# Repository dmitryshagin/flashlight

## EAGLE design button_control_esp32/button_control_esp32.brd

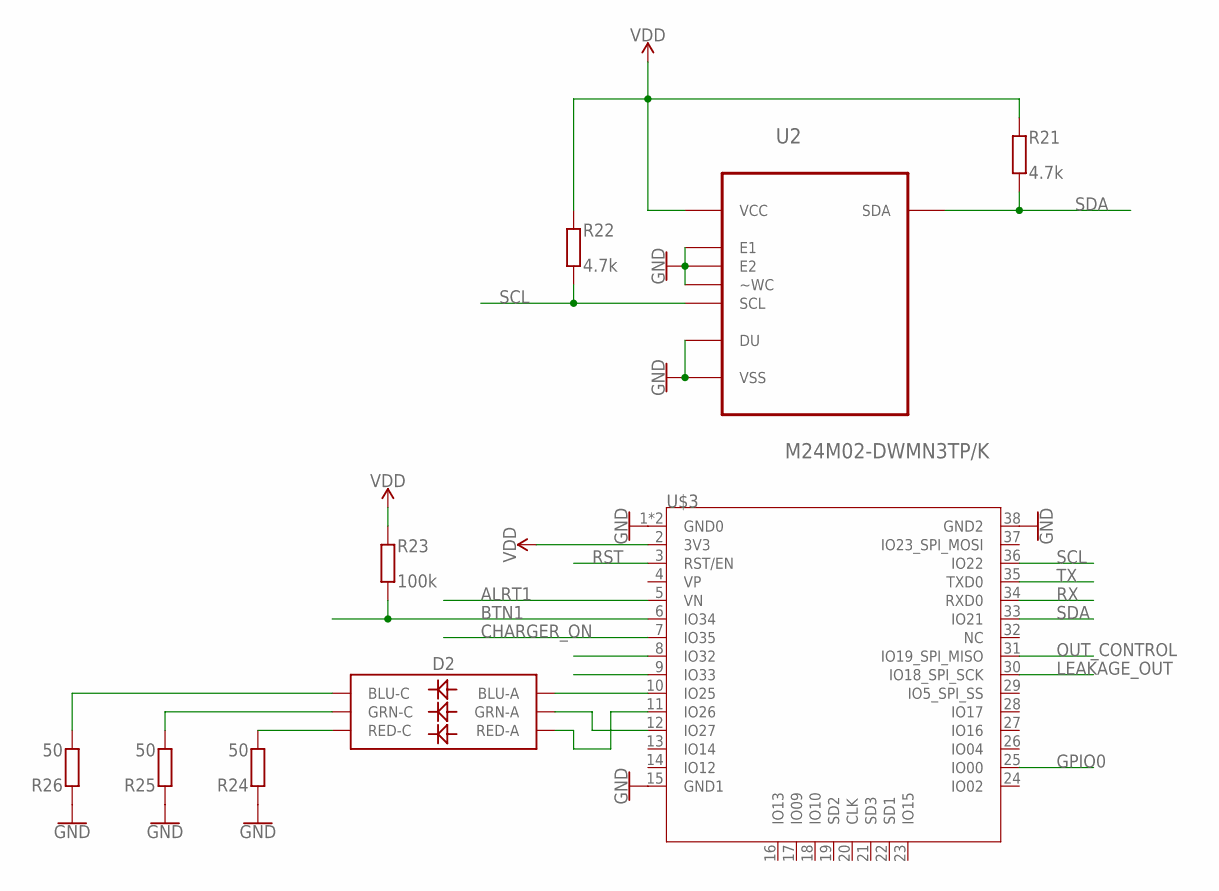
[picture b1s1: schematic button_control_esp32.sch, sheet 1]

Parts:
D2: LED-RGBNO_IC; LED-TRICOLOR-5050
R21, R22: 4.7k; R0603
R23: 100k; R0603
R24, R25, R26: 50; R0603
U2: M24M02-DWMN3TP/K; SOIC127P600X175-8N
U$3: ESP32; TTGO_ESP32

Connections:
ALRT1: U$3.5 (VN); also elsewhere on the board
BTN1: R23.1, U$3.6 (IO34); also elsewhere on the board
CHARGER_ON: U$3.7 (IO35); also elsewhere on the board
GND: R24.2, R25.2, R26.2, U2.1 (DU), U2.2 (E1), U2.3 (E2), U2.4 (VSS), U2.7 (~WC), U$3.1 (GND0), U$3.15 (GND1), U$3.38 (GND2), U$3.P$1 (GND0); also elsewhere on the board
GPIO0: U$3.25 (IO00); also elsewhere on the board
LEAKAGE_OUT: U$3.30 (IO18_SPI_SCK); also elsewhere on the board
unnamed: D2.3 (BLU-A), U$3.10 (IO25)
unnamed: D2.1 (GRN-A), U$3.12 (IO27)
unnamed: D2.2 (RED-A), U$3.11 (IO26)
unnamed: D2.4 (BLU-C), R26.1
unnamed: D2.6 (GRN-C), R25.1
unnamed: D2.5 (RED-C), R24.1
OUT_CONTROL: U$3.31 (IO19_SPI_MISO); also elsewhere on the board
RST: U$3.3 (RST/EN); also elsewhere on the board
RX: U$3.34 (RXD0); also elsewhere on the board
SCL: R22.1, U2.6 (SCL), U$3.36 (IO22); also elsewhere on the board
SDA: R21.1, U2.5 (SDA), U$3.33 (IO21); also elsewhere on the board
TX: U$3.35 (TXD0); also elsewhere on the board
VDD: R21.2, R22.2, R23.2, U2.8 (VCC), U$3.2 (3V3); also elsewhere on the board

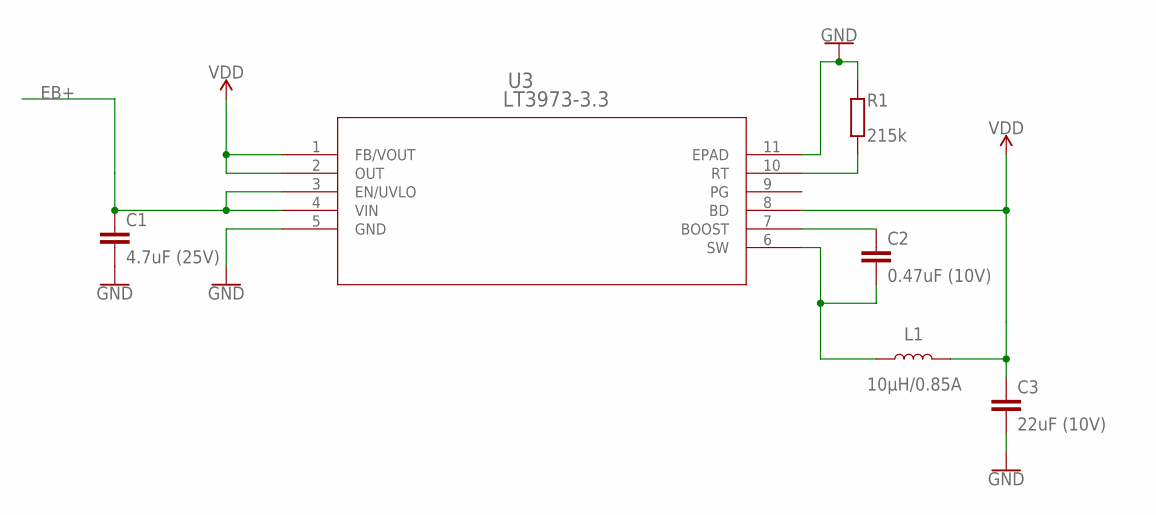
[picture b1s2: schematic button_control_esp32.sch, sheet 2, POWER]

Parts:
C1: 4.7uF (25V); C1206
C2: 0.47uF (10V); C0603K
C3: 22uF (10V); C1206
L1: 10µH/0.85A; INDUCTOR_4.7UH
R1: 215k; R0603
U3: LT3973-3.3; DFN-10_DD

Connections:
BOOST: C2.1, U3.7 (BOOST)
EB+: C1.1, U3.3 (EN/UVLO), U3.4 (VIN); also elsewhere on the board
GND: C1.2, C3.2, R1.2, U3.5 (GND), U3.11 (EPAD); also elsewhere on the board
RT: R1.1, U3.10 (RT)
SW: C2.2, L1.P$1 (1), U3.6 (SW)
VDD: C3.1, L1.P$2 (2), U3.1 (FB/VOUT), U3.2 (OUT), U3.8 (BD); also elsewhere on the board

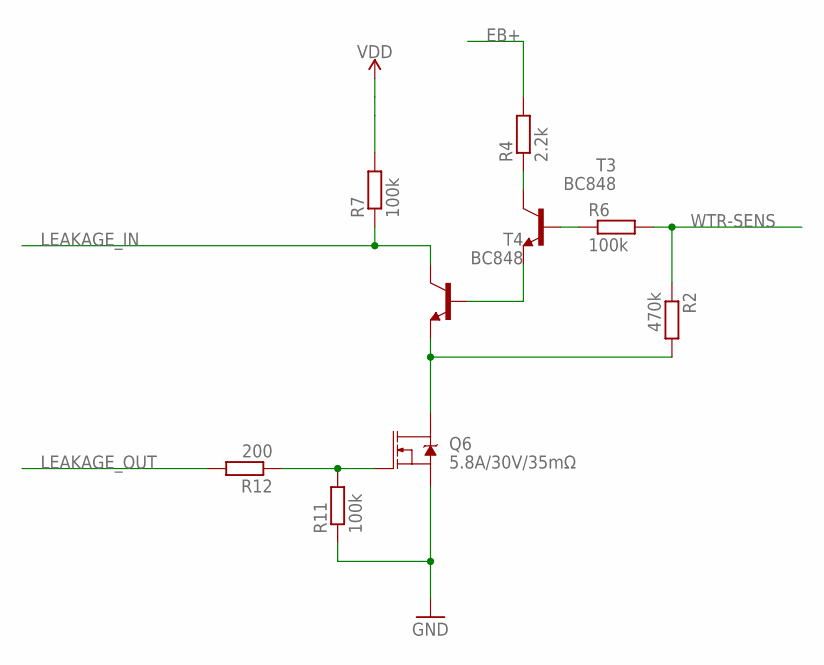
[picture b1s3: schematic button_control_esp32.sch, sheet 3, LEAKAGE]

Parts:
Q6: 5.8A/30V/35mΩ; SOT23-3
R2: 470k; R0603
R4: 2.2k; R0603
R6, R7, R11: 100k; R0603
R12: 200; R0603
T3, T4: BC848; SOT23

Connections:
EB+: R4.2; also elsewhere on the board
GND: Q6.2 (S), R11.1; also elsewhere on the board
LEAKAGE_IN: R7.1, T4.3 (C)
LEAKAGE_OUT: R12.2; also elsewhere on the board
unnamed: T3.2 (E), T4.1 (B)
unnamed: R6.1, T3.1 (B)
unnamed: Q6.3 (D), R2.2, T4.2 (E)
VDD: R7.2; also elsewhere on the board
WTR-SENS: R2.1, R6.2; also elsewhere on the board
WTR_MEASURE_ON1: Q6.1 (G), R11.2, R12.1
WTR_MEASURE_PULLUP1: R4.1, T3.3 (C)

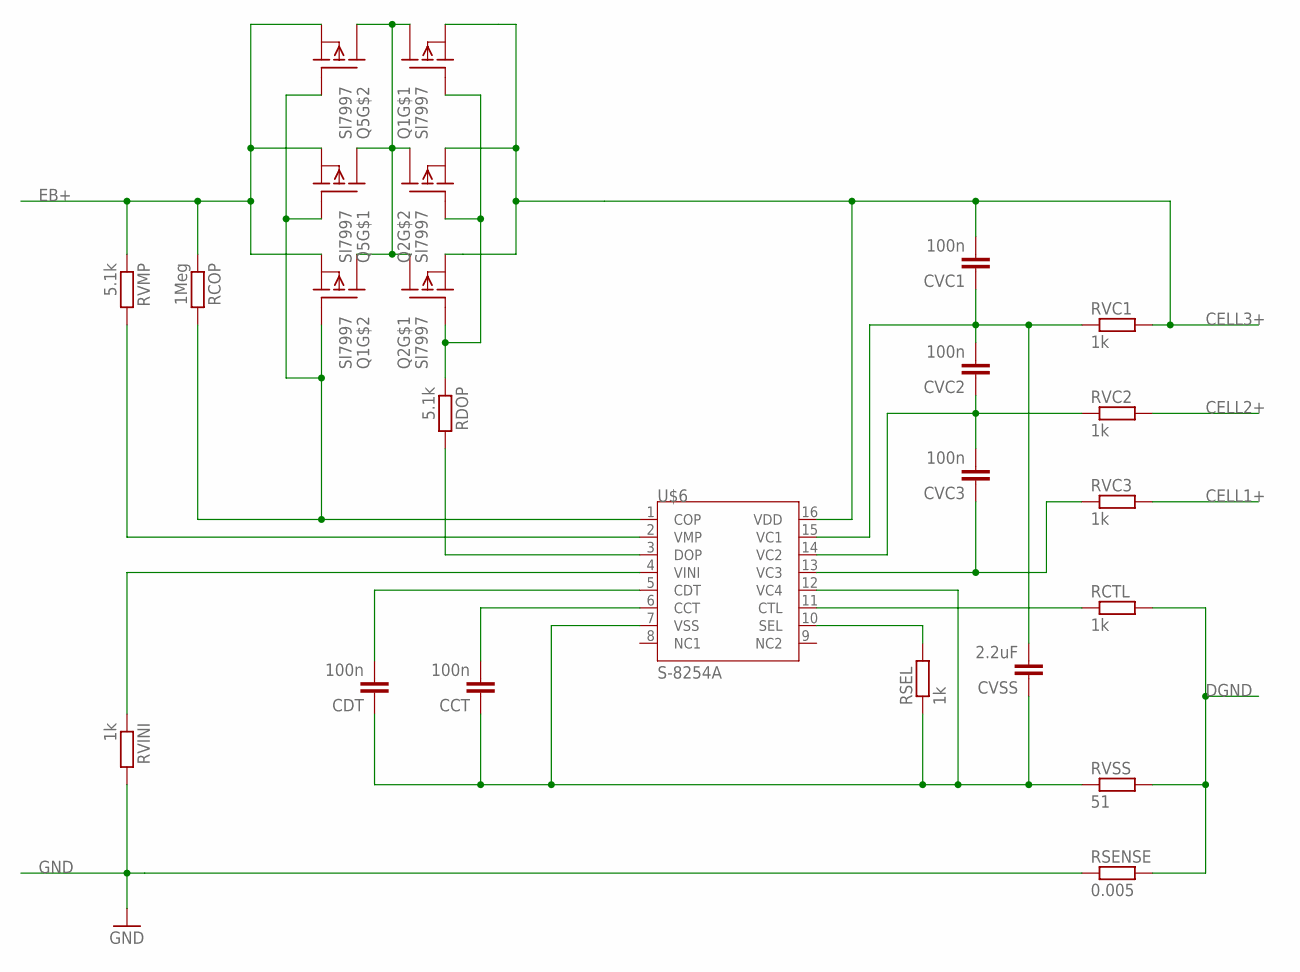
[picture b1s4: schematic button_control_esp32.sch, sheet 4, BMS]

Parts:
CCT: 100n; C0603
CDT: 100n; C0603
CVC1, CVC3: 100n; C0603
CVC2: 100n; C0805K
CVSS: 2.2uF; C0805
Q1, Q2, Q5: SI7997; POWERPAK
RCOP: 1Meg; R0603
RCTL: 1k; R0603
RDOP: 5.1k; R0603
RSEL: 1k; R0603
RSENSE: 0.005; R2010
RVC1, RVC2, RVC3: 1k; R0603
RVINI: 1k; R0603
RVMP: 5.1k; R0603
RVSS: 51; R0603
U$6: S-8254A; TSSOP-16

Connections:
CELL1+: RVC3.2; also elsewhere on the board
CELL2+: RVC2.2; also elsewhere on the board
CELL3+: CVC1.2, Q1.1 (S), Q2.1 (S), Q2.3 (S), RVC1.2, U$6.16 (VDD); also elsewhere on the board
DGND: RCTL.2, RSENSE.2, RVSS.2; also elsewhere on the board
EB+: Q1.3 (S), Q5.1 (S), Q5.3 (S), RCOP.1, RVMP.1; also elsewhere on the board
GND: RSENSE.1, RVINI.2; also elsewhere on the board
unnamed: RDOP.2, U$6.3 (DOP)
unnamed: Q1.4 (G), Q5.2 (G), Q5.4 (G), RCOP.2, U$6.1 (COP)
unnamed: Q1.2 (G), Q2.2 (G), Q2.4 (G), RDOP.1
unnamed: RVMP.2, U$6.2 (VMP)
unnamed: RSEL.2, U$6.10 (SEL)
unnamed: RVINI.1, U$6.4 (VINI)
unnamed: CDT.2, U$6.5 (CDT)
unnamed: CCT.2, U$6.6 (CCT)
unnamed: CCT.1, CDT.1, CVSS.1, RSEL.1, RVSS.1, U$6.7 (VSS), U$6.12 (VC4)
unnamed: RCTL.1, U$6.11 (CTL)
unnamed: Q1.5 (D), Q1.5_6 (D), Q1.6 (D), Q1.7 (D), Q1.7_8 (D), Q1.8 (D), Q2.5 (D), Q2.5_6 (D), Q2.6 (D), Q2.7 (D), Q2.7_8 (D), Q2.8 (D), Q5.5 (D), Q5.5_6 (D), Q5.6 (D), Q5.7 (D), Q5.7_8 (D), Q5.8 (D)
unnamed: CVC3.1, RVC3.1, U$6.13 (VC3)
unnamed: CVC2.1, CVC3.2, RVC2.1, U$6.14 (VC2)
unnamed: CVC1.1, CVC2.2, CVSS.2, RVC1.1, U$6.15 (VC1)

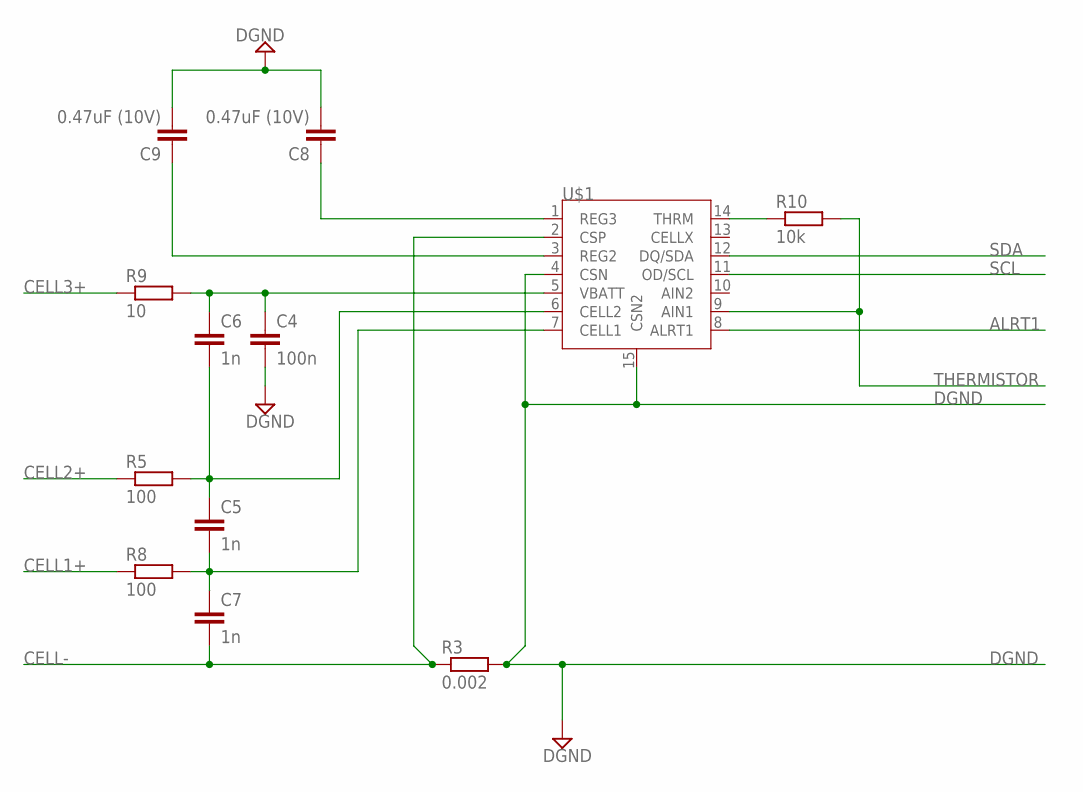
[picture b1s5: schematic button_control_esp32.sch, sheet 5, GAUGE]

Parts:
C4: 100n; C0603
C5, C6, C7: 1n; C0603
C8, C9: 0.47uF (10V); C0603K
R3: 0.002; R2010
R5, R8: 100; R0805
R9: 10; R0603
R10: 10k; R0603
U$1: MAX17205G; SON40P300X300X80-15N230X170

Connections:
ALRT1: U$1.8 (ALRT1); also elsewhere on the board
CELL1+: R8.1; also elsewhere on the board
CELL2+: R5.1; also elsewhere on the board
CELL3+: R9.1; also elsewhere on the board
CELL-: C7.2, R3.1, U$1.2 (CSP); also elsewhere on the board
DGND: C4.2, C8.2, C9.2, R3.2, U$1.4 (CSN), U$1.15 (CSN2); also elsewhere on the board
unnamed: C4.1, C6.1, R9.2, U$1.5 (VBATT)
unnamed: C5.1, C6.2, R5.2, U$1.6 (CELL2)
unnamed: C5.2, C7.1, R8.2, U$1.7 (CELL1)
unnamed: R10.1, U$1.14 (THRM)
unnamed: C8.1, U$1.1 (REG3)
unnamed: C9.1, U$1.3 (REG2)
SCL: U$1.11 (OD/SCL); also elsewhere on the board
SDA: U$1.12 (DQ/SDA); also elsewhere on the board
THERMISTOR: R10.2, U$1.9 (AIN1); also elsewhere on the board

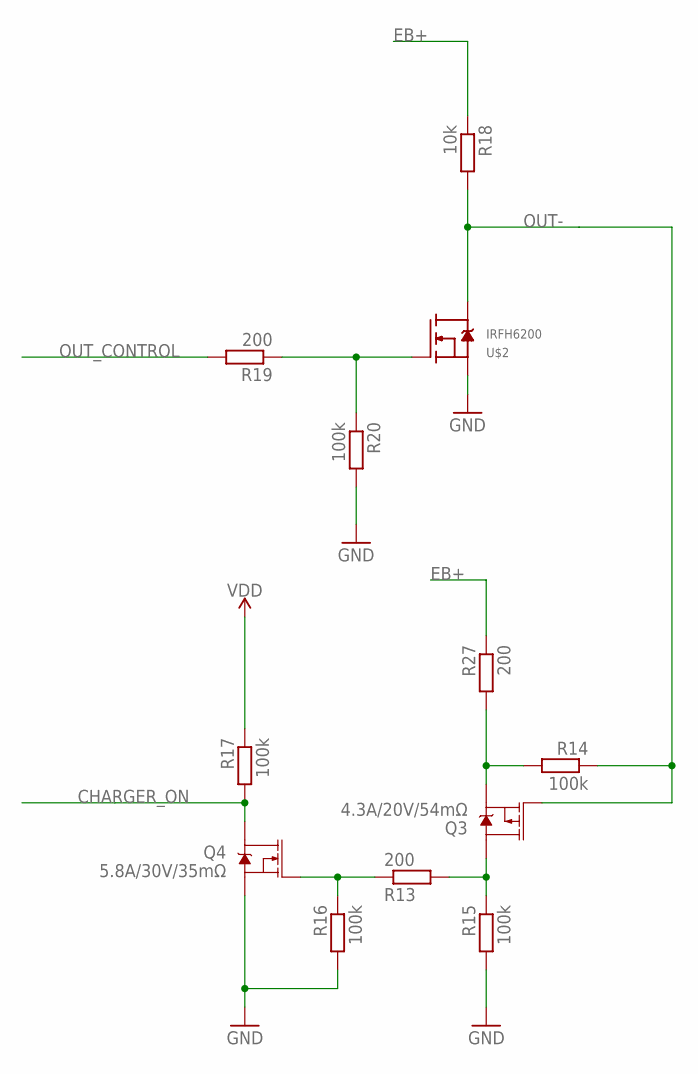
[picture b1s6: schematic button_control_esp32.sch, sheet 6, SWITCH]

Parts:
Q3: 4.3A/20V/54mΩ; SOT23-3
Q4: 5.8A/30V/35mΩ; SOT23-3
R13, R19, R27: 200; R0603
R14, R15, R16, R17, R20: 100k; R0603
R18: 10k; R0603
U$2: IRFH6200; PQFN

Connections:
CHARGER_ON: Q4.3 (D), R17.2; also elsewhere on the board
EB+: R18.1, R27.1; also elsewhere on the board
GND: Q4.2 (S), R15.2, R16.2, R20.2, U$2.1 (S), U$2.2 (S), U$2.3 (S); also elsewhere on the board
unnamed: Q3.3 (D), R13.2, R15.1
unnamed: Q4.1 (G), R13.1, R16.1
unnamed: Q3.2 (S), R14.2, R27.2
OUT-: Q3.1 (G), R14.1, R18.2, U$2.5 (D), U$2.6 (D), U$2.7 (D), U$2.8 (D), U$2.9 (D); also elsewhere on the board
OUT_BASE: R19.1, R20.1, U$2.4 (G)
OUT_CONTROL: R19.2; also elsewhere on the board
VDD: R17.1; also elsewhere on the board

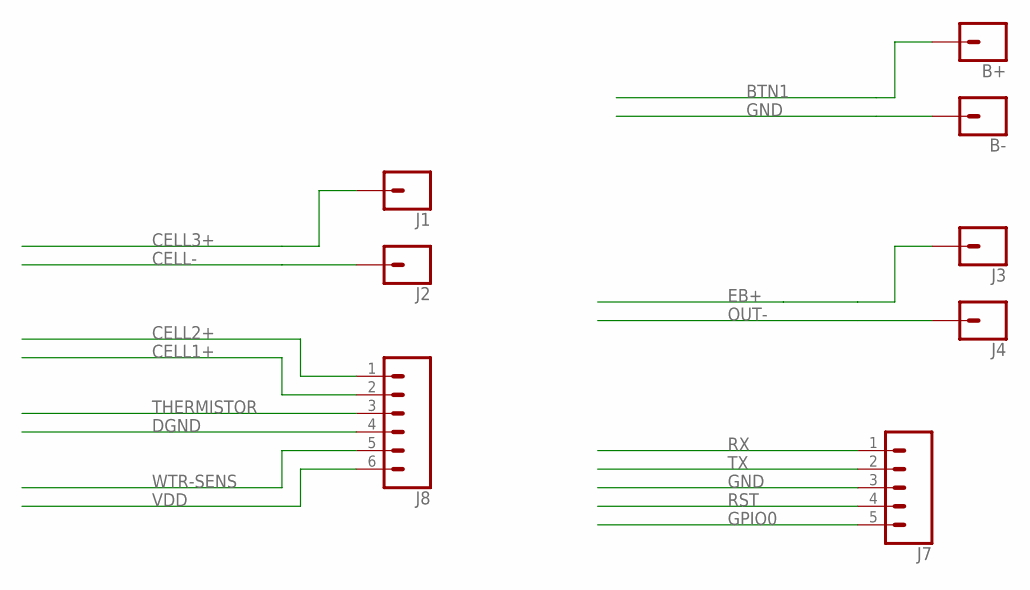
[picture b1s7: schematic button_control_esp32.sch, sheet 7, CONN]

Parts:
B+: CONN_01; 1X01
B-: CONN_01; 1X01
J1, J2, J3, J4: CONN_01PTH_2MM; 1X01_2MM
J7: CONN_051.27MM; 1X05_1.27MM
J8: CONN_061.27MM; 1X06_1.27MM

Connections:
BTN1: B+.1; also elsewhere on the board
CELL1+: J8.2; also elsewhere on the board
CELL2+: J8.1; also elsewhere on the board
CELL3+: J1.1; also elsewhere on the board
CELL-: J2.1; also elsewhere on the board
DGND: J8.4; also elsewhere on the board
EB+: J3.1; also elsewhere on the board
GND: B-.1, J7.3; also elsewhere on the board
GPIO0: J7.5; also elsewhere on the board
OUT-: J4.1; also elsewhere on the board
RST: J7.4; also elsewhere on the board
RX: J7.1; also elsewhere on the board
THERMISTOR: J8.3; also elsewhere on the board
TX: J7.2; also elsewhere on the board
VDD: J8.6; also elsewhere on the board
WTR-SENS: J8.5; also elsewhere on the board

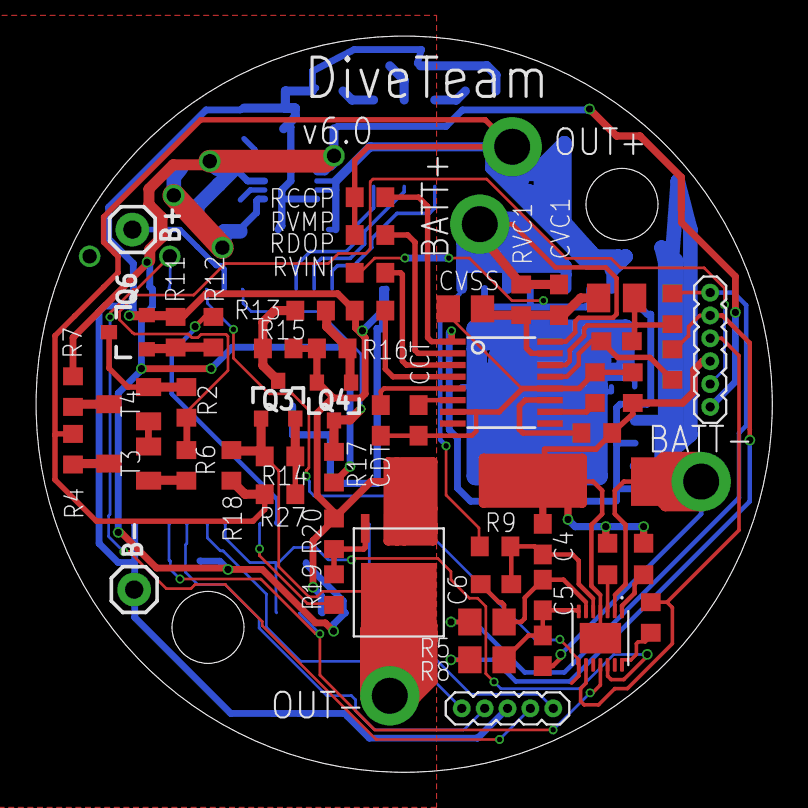
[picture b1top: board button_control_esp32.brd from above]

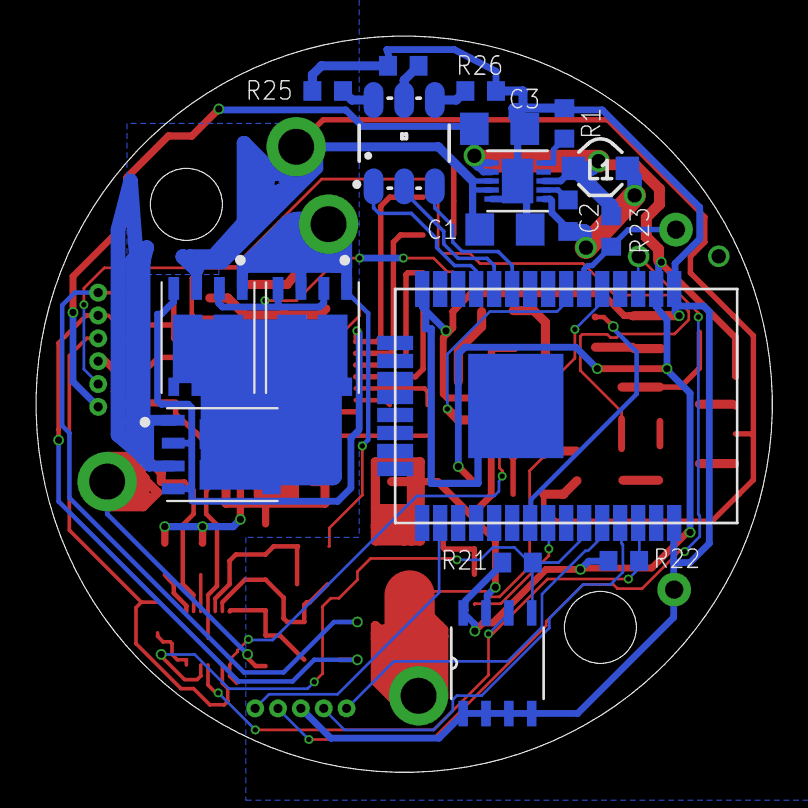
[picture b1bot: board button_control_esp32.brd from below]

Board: 2 copper layers, 40.9 x 40.9 mm, 77 parts (20 on the bottom side), 61 nets.

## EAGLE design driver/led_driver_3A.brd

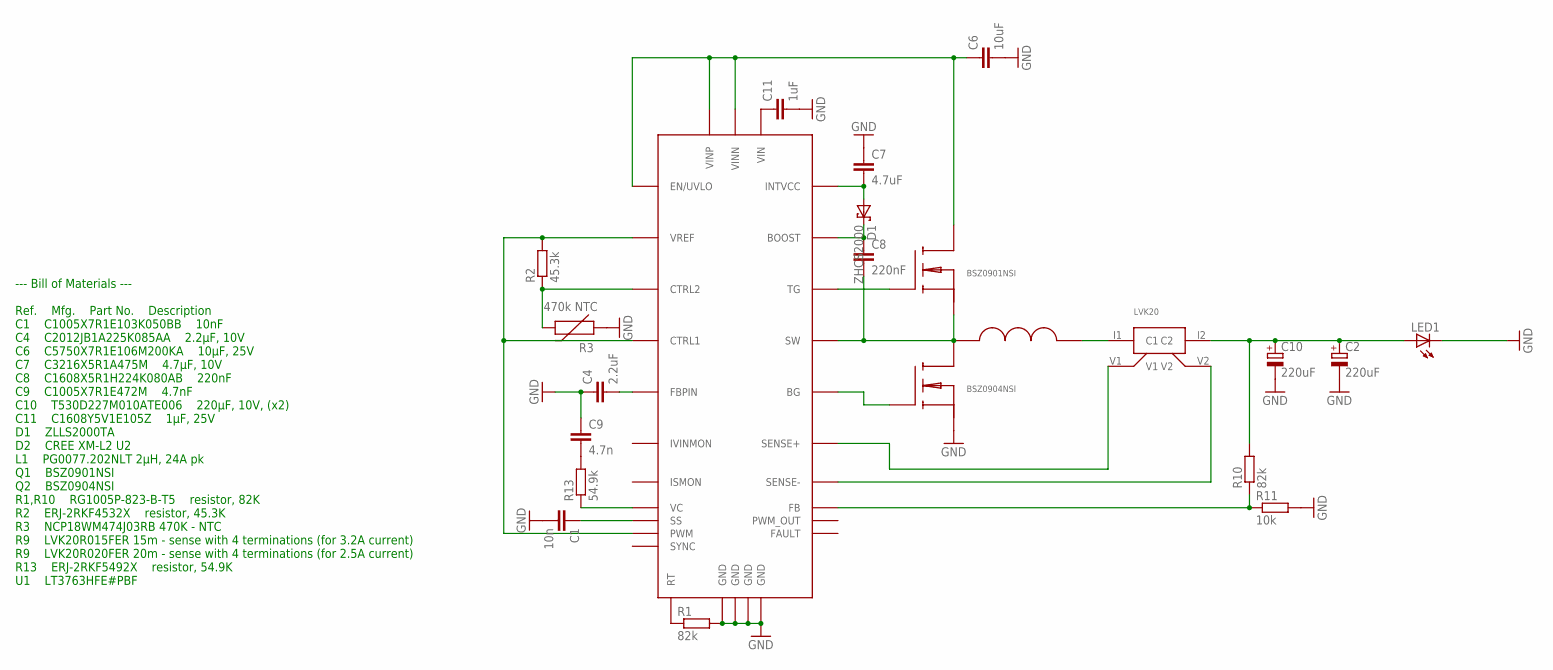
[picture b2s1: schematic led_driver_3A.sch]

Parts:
C1: 10n; C0402
C2, C10: 220uF; SMC_D
C4: 2.2uF; C0805
C6: 10uF; C2220K
C7: 4.7uF; C1206
C8: 220nF; C0603
C9: 4.7n; C0402
C11: 1uF; C0603
D1: ZHCS2000; SOT23-6
LED1: LEDSIDELED; OSRAM-SIDELED
R1, R10: 82k; R0402
R2: 45.3k; R0402
R3: 470k NTC; 0603
R11: 10k; R0402
R13: 54.9k; R0402
U$1: LT3763; TSSOP-28
U$2: PG0077
U$3: BSZ0901NSI; BSZ090X
U$4: BSZ0904NSI; BSZ090X
U$5: LVK20

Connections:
GND: C1.2, C2.-, C4.1, C6.2, C7.1, C9.1, C10.-, C11.2, LED1.C, R1.2, R3.1, R11.2, U$1.P$12 (GND), U$1.P$23 (GND), U$1.P$28 (GND), U$1.TH (GND), U$4.S@1 (S), U$4.S@2 (S), U$4.S@3 (S), U$4.S@4 (S)
unnamed: C11.1, U$1.P$3 (VIN)
unnamed: C7.2, D1.3 (A), D1.4 (A), U$1.P$2 (INTVCC)
unnamed: C9.2, R13.2
unnamed: R2.1, R3.2, U$1.P$13 (CTRL2)
unnamed: C2.+, C10.+, LED1.A, R10.2, U$5.I2 (C2)
unnamed: R1.1, U$1.P$20 (RT)
unnamed: R10.1, R11.1, U$1.P$11 (FB)
unnamed: C1.1, U$1.P$15 (SS)
unnamed: R13.1, U$1.P$18 (VC)
unnamed: C4.2, U$1.P$10 (FBPIN)
unnamed: R2.2, U$1.P$5 (VREF), U$1.P$14 (CTRL1), U$1.P$22 (PWM)
unnamed: C8.1, D1.1 (K), D1.2 (K), D1.5 (K), D1.6 (K), U$1.P$27 (BOOST)
unnamed: C8.2, U$1.P$26 (SW), U$2.P$1, U$3.S@1 (S), U$3.S@2 (S), U$3.S@3 (S), U$3.S@4 (S), U$4.D, U$4.D@1 (D), U$4.D@2 (D), U$4.D@3 (D), U$4.D@4 (D)
unnamed: U$1.P$25 (TG), U$3.G
unnamed: U$1.P$1 (BG), U$4.G
unnamed: U$1.P$17 (SENSE+), U$5.V1
unnamed: U$1.P$16 (SENSE-), U$5.V2
unnamed: U$2.P$2, U$5.I1 (C1)
VIN: C6.1, U$1.P$4 (EN/UVLO), U$1.P$6 (VINN), U$1.P$7 (VINP), U$3.D, U$3.D@1 (D), U$3.D@2 (D), U$3.D@3 (D), U$3.D@4 (D)

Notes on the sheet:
--- Bill of Materials --- Ref. Mfg. Part No. Description C1 C1005X7R1E103K050BB 10nF C4 C2012JB1A225K085AA 2.2µF, 10V C6 C5750X7R1E106M200KA 10µF, 25V C7 C3216X5R1A475M 4.7µF, 10V C8 C1608X5R1H224K080AB 220nF C9 C1005X7R1E472M 4.7nF C10 T530D227M010ATE006 220µF, 10V, (x2) C11 C1608Y5V1E105Z 1µF, 25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

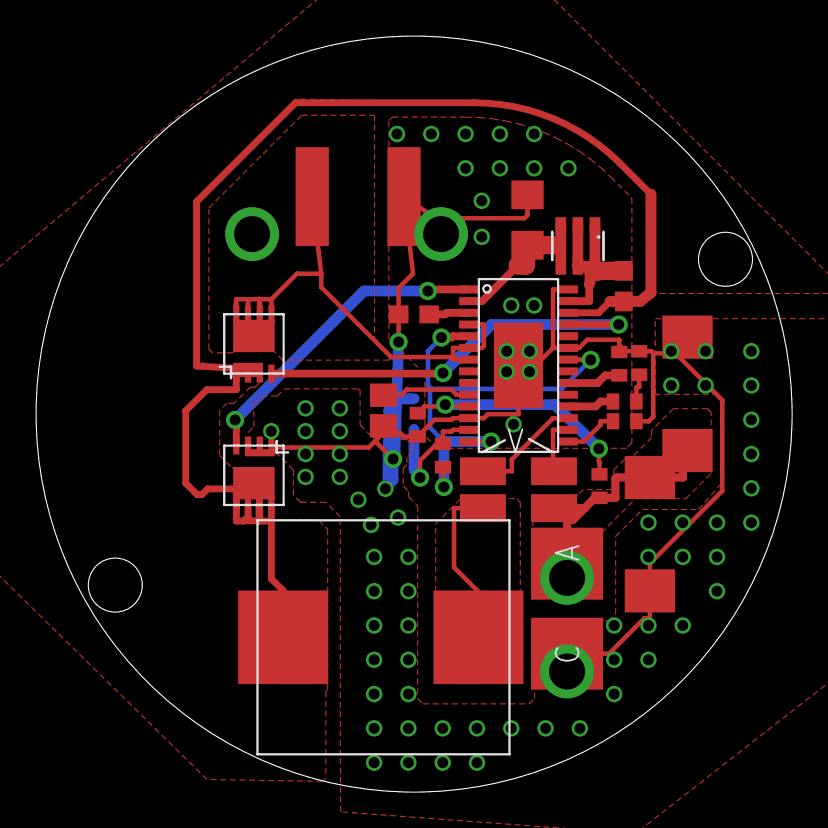
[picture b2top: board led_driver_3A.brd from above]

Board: 2 copper layers, 42.0 x 42.0 mm, 22 parts (1 on the bottom side), 20 nets.

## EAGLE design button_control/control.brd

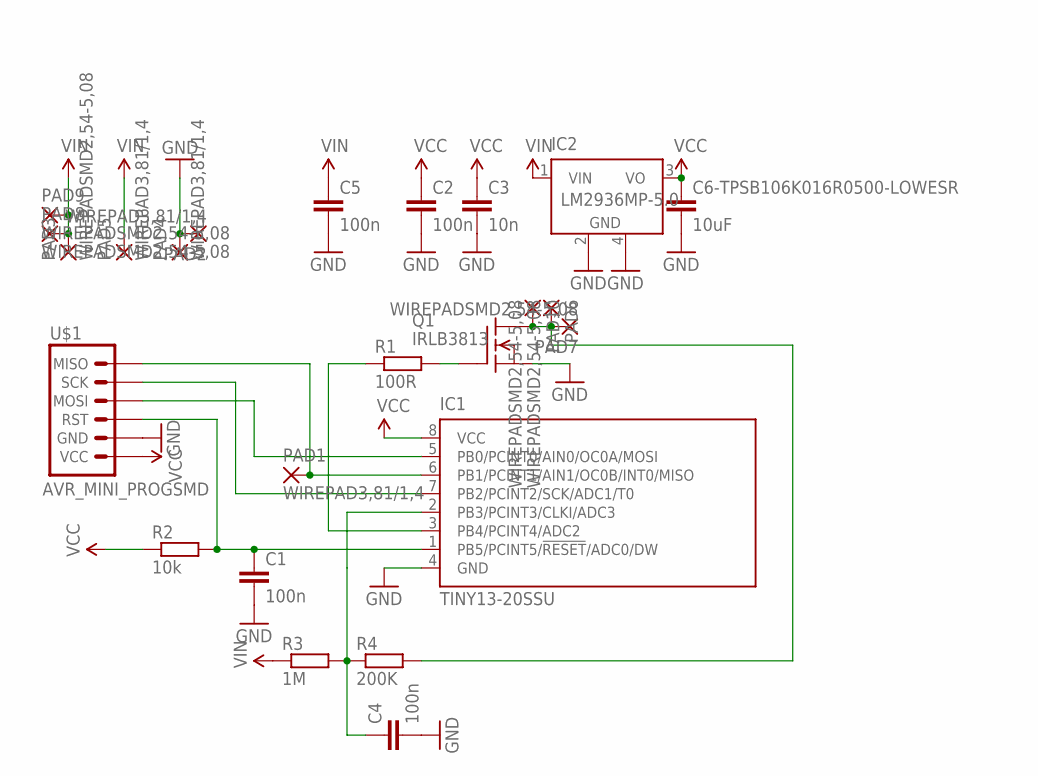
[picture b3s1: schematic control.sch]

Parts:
C1: 100n; 1210
C2, C4, C5: 100n; 1206
C3: 10n; 1206
C6-TPSB106K016R0500-LOWESR: 10uF; C1210
IC1: TINY13-20SSU; 8S1
IC2: LM2936MP-5.0; SOT223
PAD1, PAD2, PAD4, PAD5: WIREPAD3,81/1,4; 3,81/1,4
PAD3, PAD6, PAD7, PAD8, PAD9, PAD10: WIREPADSMD2,54-5,08; SMD2,54-5,08
Q1: IRLB3813; TO220
R1: 100R; M1206
R2: 10k; R1206
R3: 1M; M1206
R4: 200K; M1206
U$1: AVR_MINI_PROGSMD; AVR_MINI_PROG

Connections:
GND: C1.2, C2.2, C3.2, C4.2, C5.2, C6-TPSB106K016R0500-LOWESR.2, IC1.4 (GND), IC2.2 (GND), IC2.4 (GND), PAD2.1, PAD4.1, Q1.3 (S), U$1.2 (GND)
unnamed: IC1.6 (PB1/PCINT1/AIN1/OC0B/INT0/MISO), PAD1.1, U$1.6 (MISO)
unnamed: IC1.5 (PB0/PCINT0/AIN0/OC0A/MOSI), U$1.4 (MOSI)
unnamed: IC1.7 (PB2/PCINT2/SCK/ADC1/T0), U$1.5 (SCK)
unnamed: C1.1, IC1.1 (PB5/PCINT5/!RESET!/ADC0/DW), R2.2, U$1.3 (RST)
unnamed: Q1.1 (G), R1.2
unnamed: IC1.3 (PB4/PCINT4/ADC2), R1.1
unnamed: PAD6.1, PAD7.1, PAD10.1, Q1.2 (D), R4.2
unnamed: C4.1, IC1.2 (PB3/PCINT3/CLKI/ADC3), R3.2, R4.1
VCC: C2.1, C3.1, C6-TPSB106K016R0500-LOWESR.1, IC1.8 (VCC), IC2.3 (VO), R2.1, U$1.1 (VCC)
VIN: C5.1, IC2.1 (VIN), PAD3.1, PAD5.1, PAD8.1, PAD9.1, R3.1

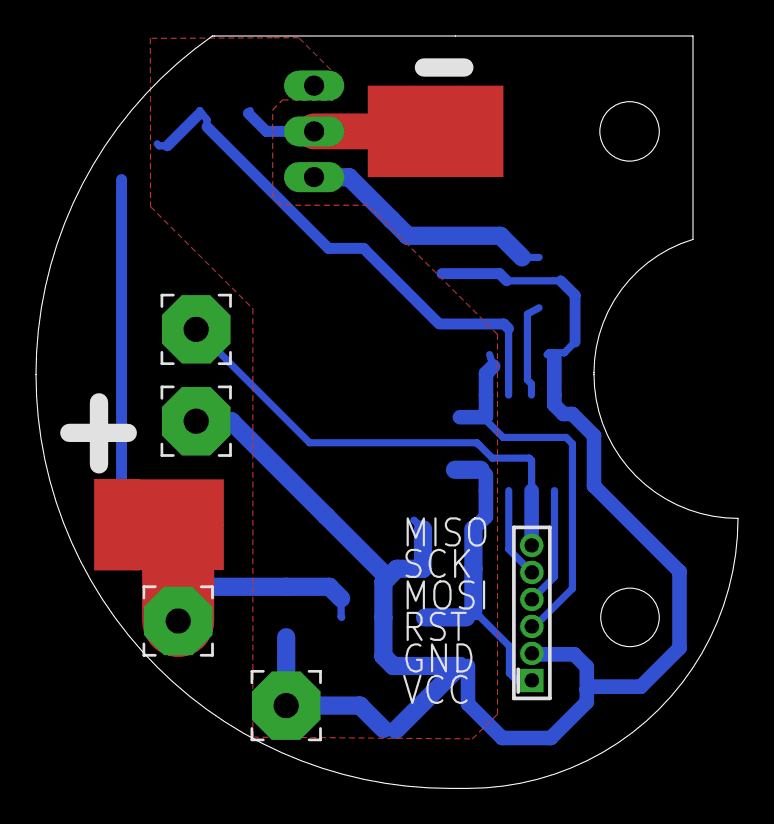
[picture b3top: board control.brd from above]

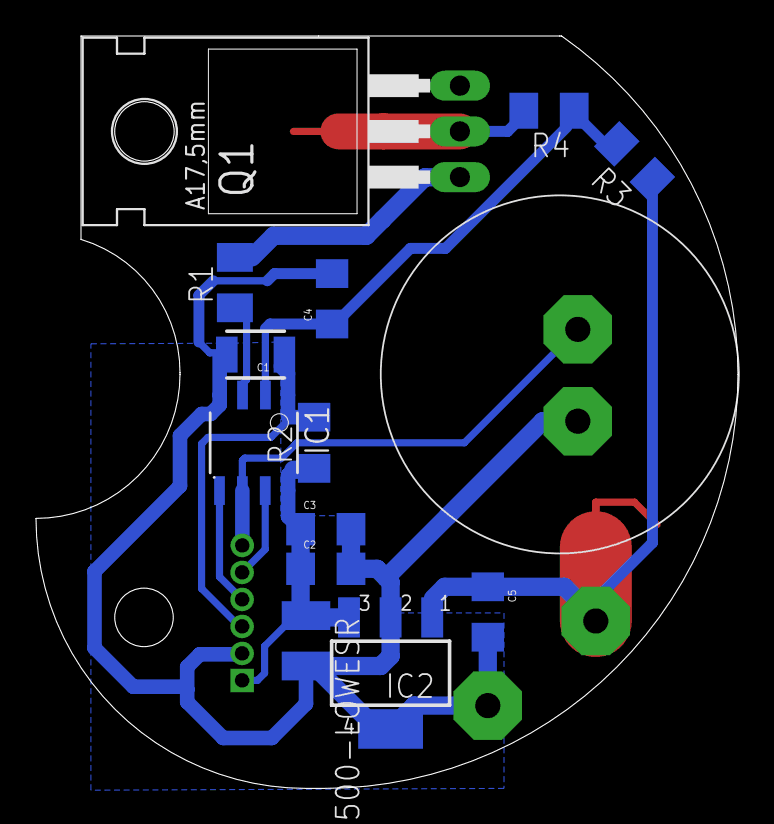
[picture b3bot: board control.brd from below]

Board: 2 copper layers, 39.0 x 41.8 mm, 24 parts (13 on the bottom side), 11 nets.

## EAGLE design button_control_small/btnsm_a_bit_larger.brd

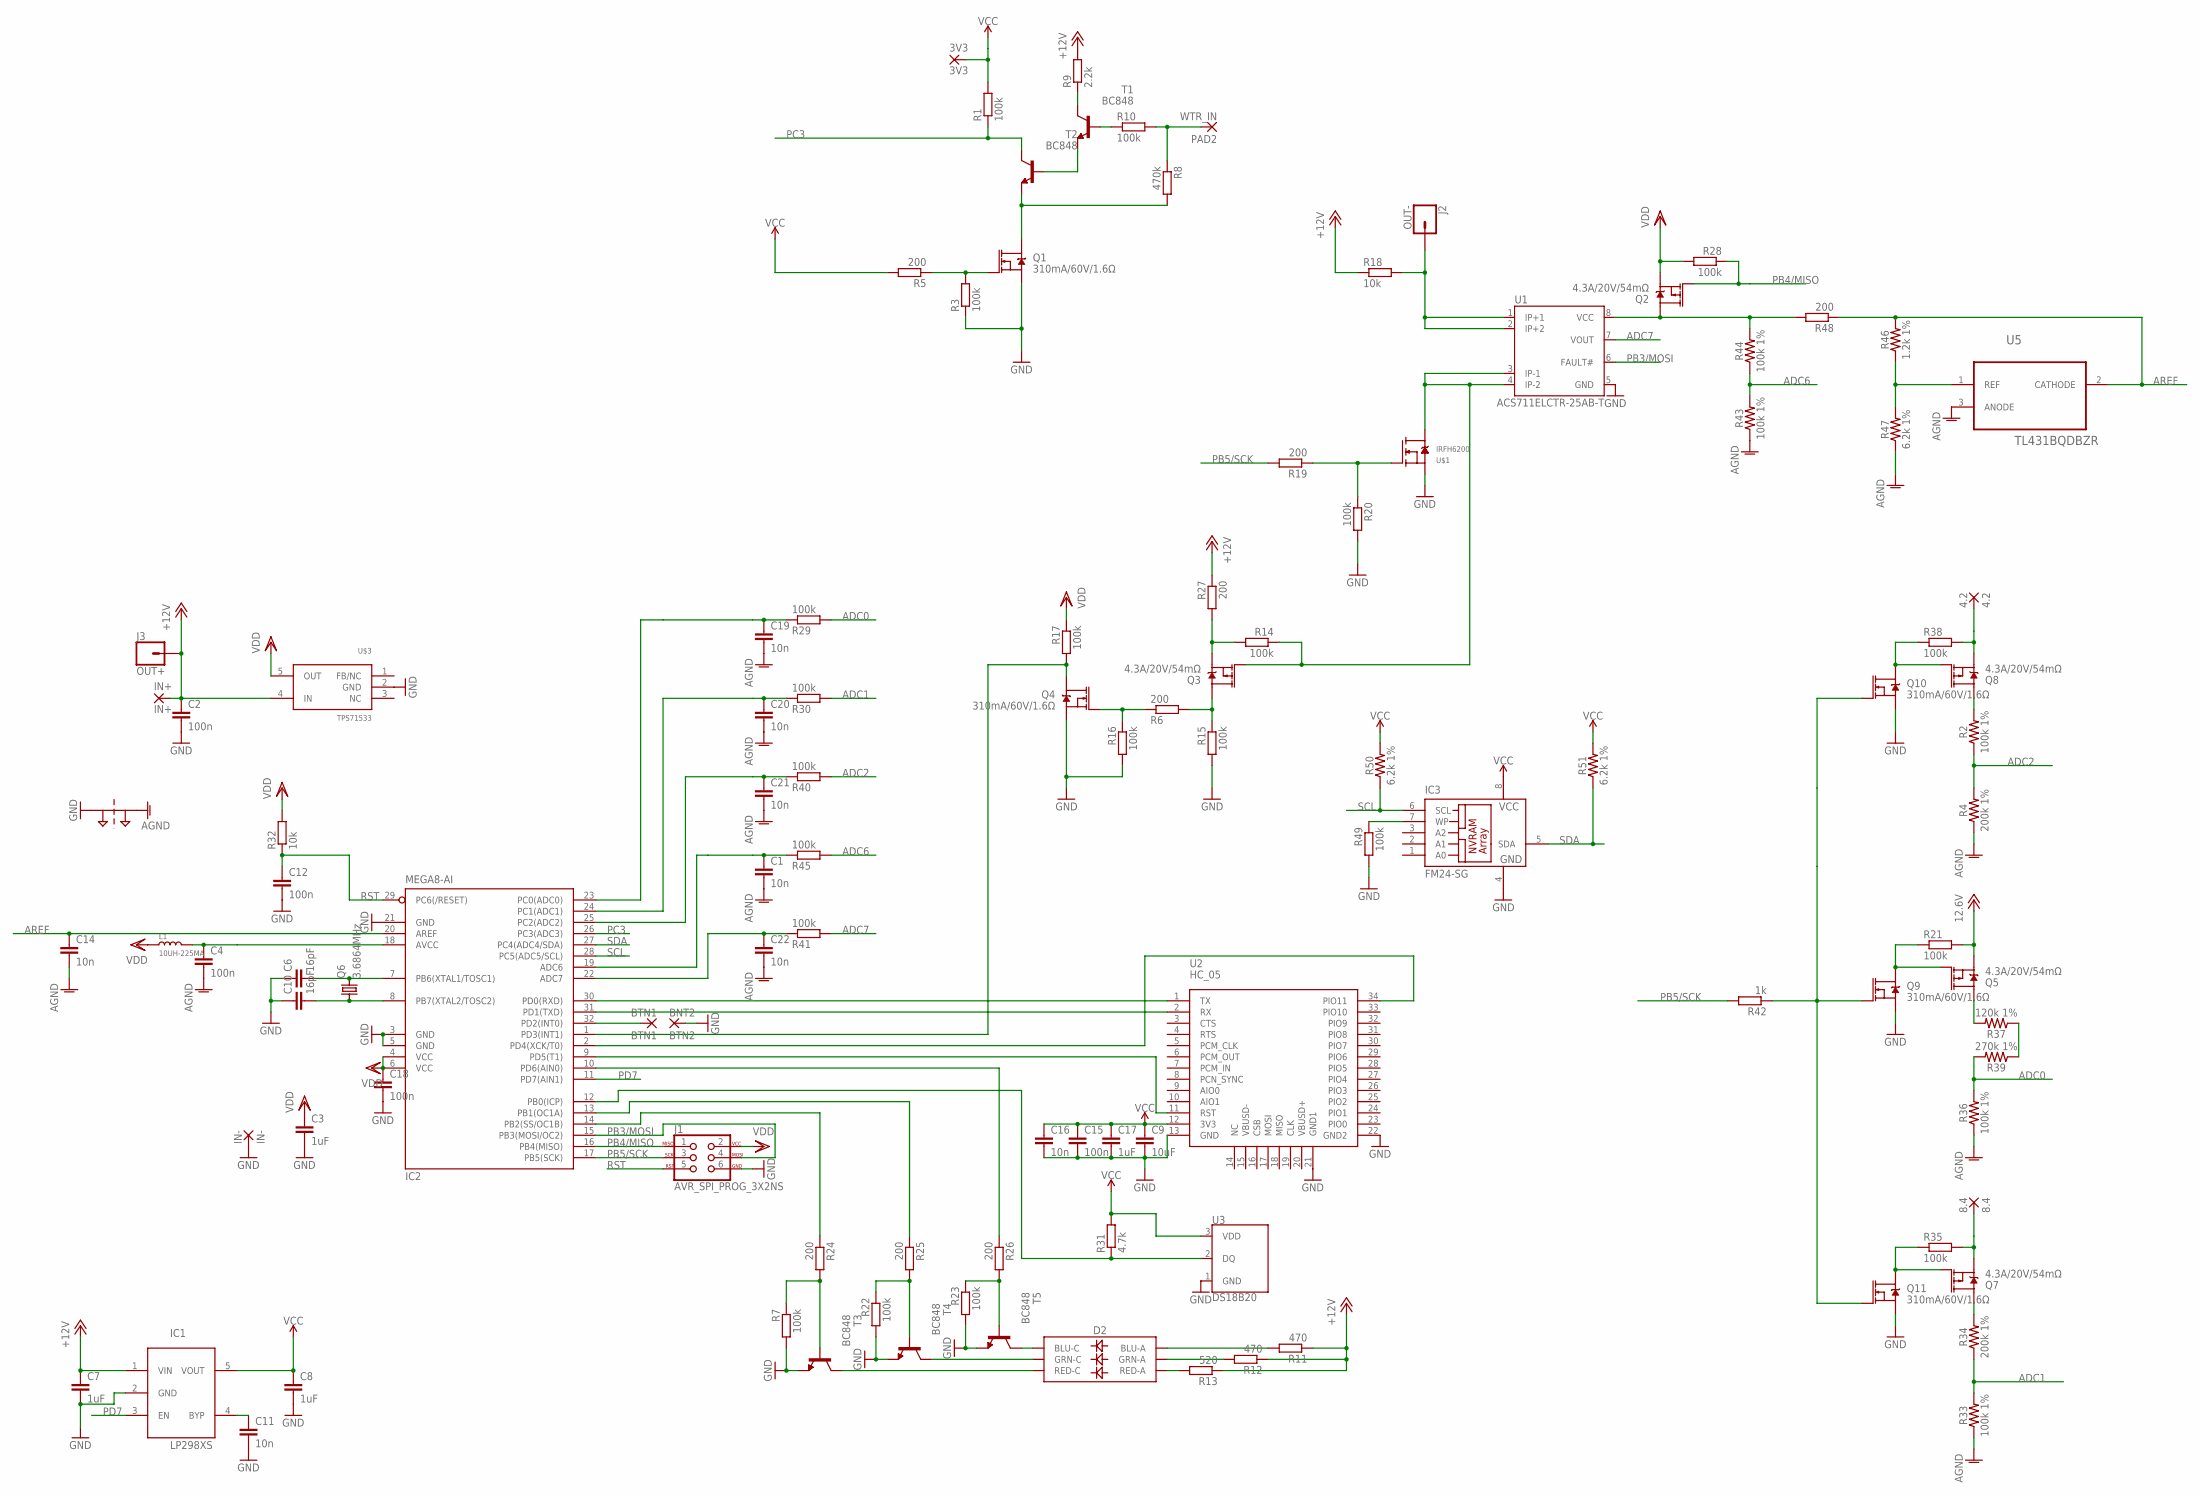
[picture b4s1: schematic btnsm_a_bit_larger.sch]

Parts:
3V3: 3V3; SMD1,27-2,54
4.2: 4.2; SMD1,27-2,54
8.4: 8.4; SMD1,27-2,54
BTN1: BTN1; 1,6/0,9
BTN2: BNT2; 1,6/0,9
C1, C11, C14, C16, C19, C20, C21, C22: 10n; C0402
C2: 100n; C0603
C3, C7, C8, C17: 1uF; C0805
C4, C12, C15, C18: 100n; C0402
C6, C10: 16pF; C0402
C9: 10uF; C0805
D2: LED-RGBNO_IC; LED-TRICOLOR-5050
IC1: LP298XS; SOT23-5L
IC2: MEGA8-AI; TQFP32-08
IC3: FM24-SG; SO8
IN+: IN+; SMD2,54-5,08
IN-: IN-; SMD2,54-5,08
J1: AVR_SPI_PROG_3X2NS; 2X3-NS
J2: OUT-; 1X01_2MM
J3: OUT+; 1X01_2MM
L1: 10UH-225MA; L0806
PAD2: WTR_IN; SMD1,27-2,54
Q1, Q4, Q9, Q10, Q11: 310mA/60V/1.6Ω; SOT323
Q2, Q3, Q5, Q7, Q8: 4.3A/20V/54mΩ; SOT23-3
Q6: 3.6864MHz; HC49/S
R1, R3, R7, R10, R14, R15, R16, R17, R20, R21, R22, R23, R28, R29, R30, R35, R38, R40, R41, R45, R49: 100k; R0402
R2, R33, R36, R43, R44: 100k 1%; 0805
R4, R34: 200k 1%; 0805
R5, R6, R19, R24, R25, R26, R27, R48: 200; R0402
R8: 470k; R0402
R9: 2.2k; R0402
R11, R12: 470; R0805
R13: 520; R0805
R18, R32: 10k; R0402
R31: 4.7k; R0402
R37: 120k 1%; 0805
R39: 270k 1%; 0805
R42: 1k; R0402
R46: 1.2k 1%; 0805
R47, R50, R51: 6.2k 1%; 0805
SUPPLY7: 2PT_GND_TIE
T1, T2, T3, T4, T5: BC848; SOT23
U1: ACS711ELCTR-25AB-T; SOIC8
U2: HC_05; BLUETOOTH_SMD
U3: DS18B20; TO-92-AMMO
U5: TL431BQDBZR; SOT95P237X112-3N
U$1: IRFH6200; PQFN
U$3: TPS71533; SC70

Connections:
+12V: C2.1, C7.1, IC1.1 (VIN), IN+.1, J3.1, Q5.2 (S), R9.2, R11.1, R12.1, R13.1, R18.1, R21.2, R27.1, U$3.4 (IN)
ADC0: R29.2, R36.2, R39.2
ADC1: R30.2, R33.2, R34.1
ADC2: R2.1, R4.2, R40.2
ADC6: R43.2, R44.1, R45.2
ADC7: R41.2, U1.7 (VOUT)
AGND: C1.2, C4.2, C14.2, C19.2, C20.2, C21.2, C22.2, R4.1, R33.1, R36.1, R43.1, R47.1, SUPPLY7.P$2, U5.3 (ANODE)
AREF: C14.1, IC2.20 (AREF), R46.2, R48.1, U5.2 (CATHODE)
AVCC: C4.1, IC2.18 (AVCC), L1.2
B+: D2.3 (BLU-A), R11.2
B-: D2.4 (BLU-C), T5.3 (C)
B-BASE: R23.1, R26.2, T5.1 (B)
BTN1: BTN1.1, IC2.32 (PD2(INT0))
G+: D2.1 (GRN-A), R12.2
G-: D2.6 (GRN-C), T4.3 (C)
G-BASE: R22.1, R25.2, T4.1 (B)
GND: BTN2.1, C2.2, C3.2, C6.1, C7.2, C8.2, C9.2, C10.1, C11.2, C12.2, C15.2, C16.2, C17.2, C18.2, IC1.2 (GND), IC2.3 (GND), IC2.5 (GND), IC2.21 (GND), IC3.4 (GND), IN-.1, J1.6, Q1.2 (S), Q4.2 (S), Q9.2 (S), Q10.2 (S), Q11.2 (S), R3.1, R7.2, R15.2, R16.2, R20.2, R22.2, R23.2, R49.2, SUPPLY7.P$1, T3.2 (E), T4.2 (E), T5.2 (E), U1.5 (GND), U2.13 (GND), U2.21 (GND1), U2.22 (GND2), U3.1 (GND), U$1.1 (S), U$1.2 (S), U$1.3 (S), U$3.2 (GND)
GND_OUT: J2.1, R18.2, U1.1 (IP+1), U1.2 (IP+2)
GND_OUT_MEASURE: Q3.1 (G), R14.1, U1.3 (IP-1), U1.4 (IP-2), U$1.5 (D), U$1.6 (D), U$1.7 (D), U$1.8 (D), U$1.9 (D)
unnamed: Q4.1 (G), R6.1, R16.1
unnamed: C11.1, IC1.4 (BYP)
unnamed: Q7.1 (G), Q11.3 (D), R35.1
unnamed: Q1.3 (D), R8.2, T2.2 (E)
unnamed: Q7.3 (D), R34.2
unnamed: Q8.1 (G), Q10.3 (D), R38.1
unnamed: Q8.3 (D), R2.2
unnamed: R37.1, R39.1
unnamed: Q3.3 (D), R6.2, R15.1
unnamed: 8.4.1, Q7.2 (S), R35.2
unnamed: Q5.1 (G), Q9.3 (D), R21.1
unnamed: 4.2.1, Q8.2 (S), R38.2
unnamed: T1.2 (E), T2.1 (B)
unnamed: Q2.3 (D), R44.2, R48.2, U1.8 (VCC)
unnamed: R10.1, T1.1 (B)
unnamed: Q9.1 (G), Q10.1 (G), Q11.1 (G), R42.1
unnamed: Q5.3 (D), R37.2
unnamed: IC3.7 (WP), R49.1
unnamed: Q3.2 (S), R14.2, R27.2
OUT_BASE: R19.1, R20.1, U$1.4 (G)
PB0: IC2.12 (PB0(ICP)), R31.1, U3.2 (DQ)
PB1: IC2.13 (PB1(OC1A)), R25.1
PB2: IC2.14 (PB2(SS/OC1B)), R24.1
PB3/MOSI: IC2.15 (PB3(MOSI/OC2)), J1.4, U1.6 (FAULT#)
PB4/MISO: IC2.16 (PB4(MISO)), J1.1, Q2.1 (G), R28.1
PB5/SCK: IC2.17 (PB5(SCK)), J1.3, R19.2, R42.2
PB6: C6.2, IC2.7 (PB6(XTAL1/TOSC1)), Q6.2
PB7: C10.2, IC2.8 (PB7(XTAL2/TOSC2)), Q6.1
PC3: IC2.26 (PC3(ADC3)), R1.1, T2.3 (C)
PD3: IC2.1 (PD3(INT1)), Q4.3 (D), R17.2
PD4-HC05_KEY: IC2.2 (PD4(XCK/T0)), U2.34 (PIO11)
PD5-HC05_RST: IC2.9 (PD5(T1)), U2.11 (RST)
PD6(PWM0): IC2.10 (PD6(AIN0)), R26.1
PD7: IC1.3 (EN), IC2.11 (PD7(AIN1))
R+: D2.2 (RED-A), R13.2
R-: D2.5 (RED-C), T3.3 (C)
R-BASE: R7.1, R24.2, T3.1 (B)
REF: R46.1, R47.2, U5.1 (REF)
RST: C12.1, IC2.29 (PC6(/RESET)), J1.5, R32.1
RX(UC): IC2.30 (PD0(RXD)), U2.1 (TX)
SCL: IC2.28 (PC5(ADC5/SCL)), IC3.6 (SCL), R50.1
SDA: IC2.27 (PC4(ADC4/SDA)), IC3.5 (SDA), R51.1
TX(UC): IC2.31 (PD1(TXD)), U2.2 (RX)
VCC: 3V3.1, C8.1, C9.1, C15.1, C16.1, C17.1, IC1.5 (VOUT), IC3.8 (VCC), R1.2, R5.2, R31.2, R50.2, R51.2, U2.12 (3V3), U3.3 (VDD)
VDD: C3.1, C18.1, IC2.4 (VCC), IC2.6 (VCC), J1.2, L1.1, Q2.2 (S), R17.1, R28.2, R32.2, U$3.5 (OUT)
WTR-IN: PAD2.1, R8.1, R10.2
WTR_MEASURE_ON: Q1.1 (G), R3.2, R5.1
WTR_MEASURE_PULLUP: R9.1, T1.3 (C)
_A0: C19.1, IC2.23 (PC0(ADC0)), R29.1
_A1: C20.1, IC2.24 (PC1(ADC1)), R30.1
_A2: C21.1, IC2.25 (PC2(ADC2)), R40.1
_A6: C1.1, IC2.19 (ADC6), R45.1
_A7: C22.1, IC2.22 (ADC7), R41.1

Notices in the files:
parts and their libraries:
SparkFun-Connectors: Licensing: CC v3.0 Share-Alike You are welcome to use this library for commercial purposes.
SparkFun-LED: Licensing: Creative Commons ShareAlike 4.0 International - https://creativecommons.org/licenses/by-sa/4.0
